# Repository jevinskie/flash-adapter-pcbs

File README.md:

# flash-adapter-pcbs
Various PCB adapters for flash memories and devices that use them

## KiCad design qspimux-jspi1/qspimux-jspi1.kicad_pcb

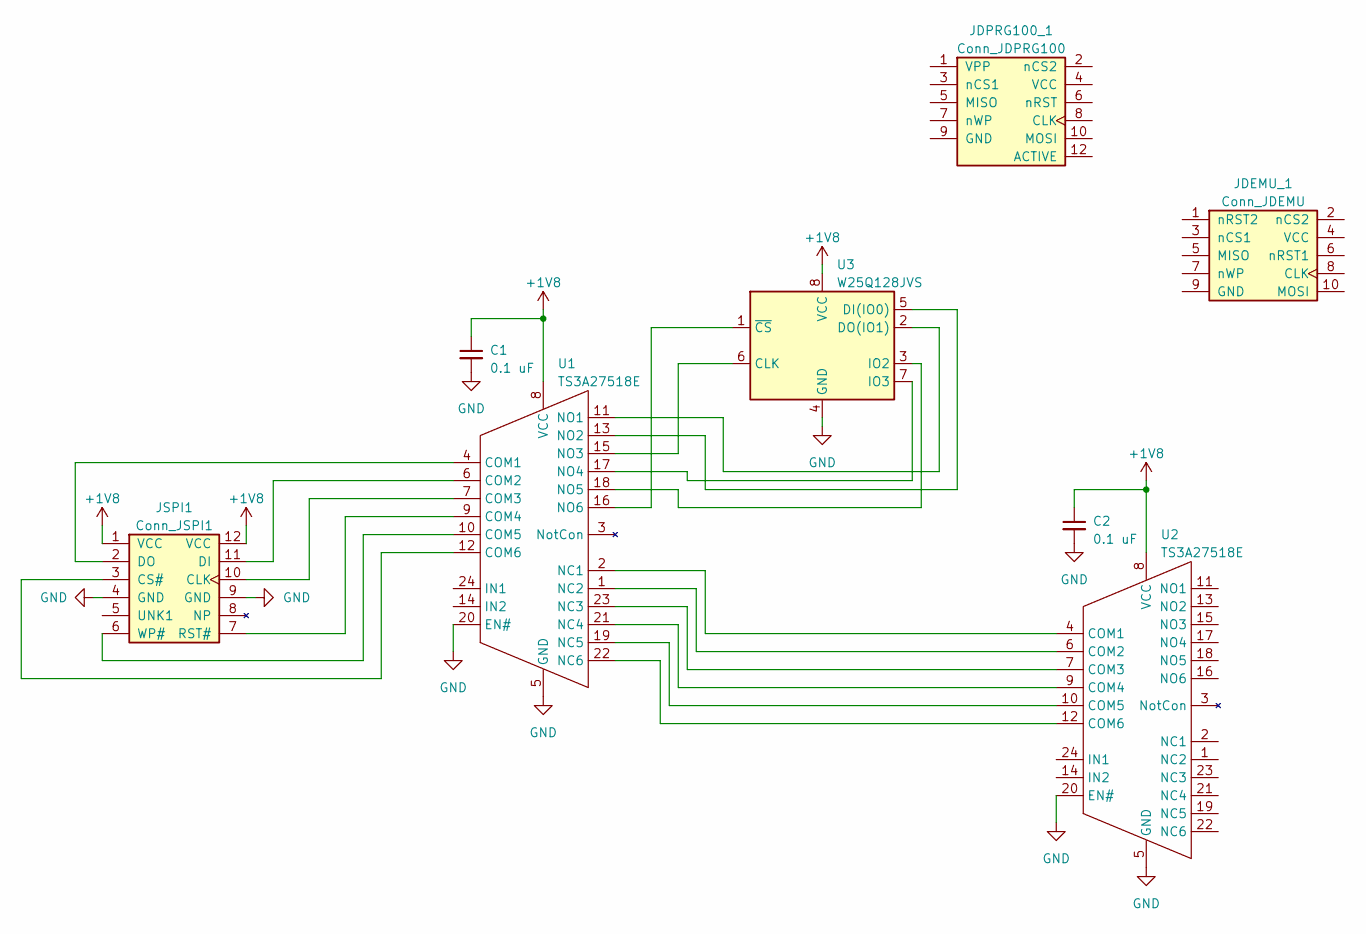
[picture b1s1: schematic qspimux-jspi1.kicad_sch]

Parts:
C1, C2: 0.1 uF; C_0603_1608Metric_Pad1.08x0.95mm_HandSolder
JDEMU_1: Conn_JDEMU; PinHeader_2x05_P2.54mm_Vertical
JDPRG100_1: Conn_JDPRG100; PinHeader_2x06_P2.54mm_Vertical
JSPI1: Conn_JSPI1; PinSocket_2x06_P1.27mm_Horizontal
U1, U2: TS3A27518E; TSSOP-24_6.1x7.8mm_P0.65mm
U3: W25Q128JVS; SOIC-8_5.23x5.23mm_P1.27mm

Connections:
+1V8: C1.1, C2.1, JSPI1.1 (VCC), JSPI1.12 (VCC), U1.8 (VCC), U2.8 (VCC), U3.8 (VCC)
GND: C1.2, C2.2, JSPI1.4 (GND), JSPI1.9 (GND), U1.5 (GND), U1.20 (EN#), U2.5 (GND), U2.20 (EN#), U3.4 (GND)
unnamed: JSPI1.10 (CLK), U1.7 (COM3)
unnamed: JSPI1.3 (CS#), U1.12 (COM6)
unnamed: JSPI1.11 (DI), U1.6 (COM2)
unnamed: JSPI1.2 (DO), U1.4 (COM1)
unnamed: JSPI1.7 (RST#), U1.9 (COM4)
unnamed: JSPI1.6 (WP#), U1.10 (COM5)
unnamed: U1.2 (NC1), U2.4 (COM1)
unnamed: U1.1 (NC2), U2.6 (COM2)
unnamed: U1.23 (NC3), U2.7 (COM3)
unnamed: U1.21 (NC4), U2.9 (COM4)
unnamed: U1.19 (NC5), U2.10 (COM5)
unnamed: U1.22 (NC6), U2.12 (COM6)
unnamed: U1.11 (NO1), U3.2 (DO(IO1))
unnamed: U1.13 (NO2), U3.5 (DI(IO0))
unnamed: U1.15 (NO3), U3.6 (CLK)
unnamed: U1.17 (NO4), U3.7 (IO3)
unnamed: U1.18 (NO5), U3.3 (IO2)
unnamed: U1.16 (NO6), U3.1 (~CS)

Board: 2 copper layers, 8 parts (1 on the bottom side), 20 nets, no tracks yet.

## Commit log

2022-02-15 Create LICENSE
2022-02-16 kicad .gitignore
2022-02-16 ignore in any dir
